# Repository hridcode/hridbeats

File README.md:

# hridBeats
hridBeats is an open-source sample chopper, synth, and MIDI controller based off the Raspberry Pi Pico. 

# Features

- 12 touchpads
- 8 potentiometers
- rotary encoder with a pushbutton
- joystick for mouse control
- TFT LCD 2.0" ST7789 display
- PCM5102A I2S DAC board for audio output
- SD card slot for loading songs/samples
- MIDI through USB
- Mini synth engine

# Pictures

|Schematic|PCB|Case|
|---|---|---|
||||

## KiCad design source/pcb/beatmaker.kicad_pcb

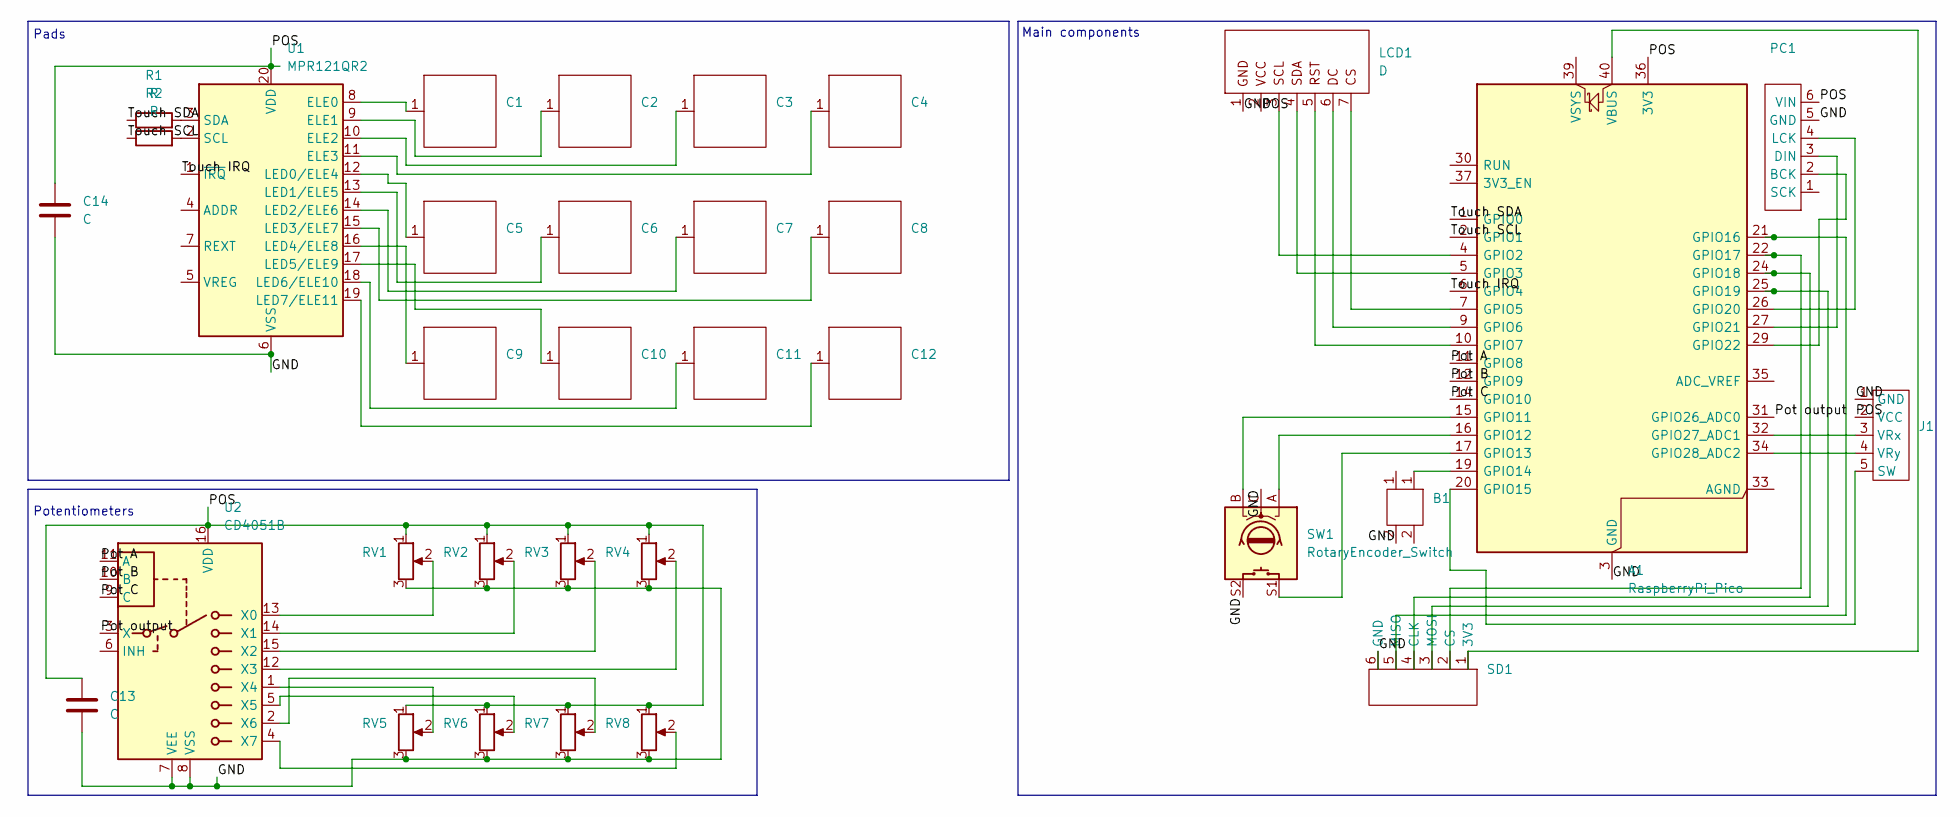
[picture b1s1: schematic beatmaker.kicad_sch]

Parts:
A1: RaspberryPi_Pico; RaspberryPi_Pico_Common_Unspecified
B1: SW_PUSH_6mm
C1, C2, C3, C4, C5, C6, C7, C8, C9, C10, C11, C12: copper_pad_25mm
C13, C14: C; CP_Radial_D4.0mm_P1.50mm
J1: ky-023-joystick
LCD1: D; ST7789
PC1: PCM5201-Board
R1, R2: R; R_Axial_DIN0204_L3.6mm_D1.6mm_P1.90mm_Vertical
RV1, RV2, RV3, RV4, RV5, RV6, RV7, RV8: R_Potentiometer; potentiometer
SD1: sd_card_module
SW1: RotaryEncoder_Switch; RotaryEncoder_Alps_EC11E-Switch_Vertical_H20mm_MountingHoles
U1: MPR121QR2; UQFN-20_3x3mm_P0.4mm
U2: CD4051B; DIP-16_W7.62mm

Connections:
/GND: A1.3 (GND), A1.8 (GND), A1.13 (GND), A1.18 (GND), A1.23 (GND), A1.28 (GND), A1.38 (GND), B1.2, C13.2, C14.2, J1.1 (GND), LCD1.1, PC1.5 (GND), RV1.3, RV2.3, RV3.3, RV4.3, RV5.3, RV6.3, RV7.3, RV8.3, SD1.6 (GND), SW1.C, SW1.S2, U1.6 (VSS), U2.7 (VEE), U2.8 (VSS)
/POS: A1.36 (3V3), C13.1, C14.1, J1.2 (VCC), LCD1.2, PC1.6 (VIN), RV1.1, RV2.1, RV3.1, RV4.1, RV5.1, RV6.1, RV7.1, RV8.1, U1.20 (VDD), U2.16 (VDD)
/Pot A: A1.11 (GPIO8), U2.11 (A)
/Pot B: A1.12 (GPIO9), U2.10 (B)
/Pot C: A1.14 (GPIO10), U2.9 (C)
/Pot output: A1.31 (GPIO26_ADC0), U2.3 (X)
/Touch IRQ: A1.6 (GPIO4), U1.1 (~IRQ)
/Touch SCL: A1.2 (GPIO1), R2.1
/Touch SDA: A1.1 (GPIO0), R1.1
unnamed: A1.4 (GPIO2), LCD1.3
unnamed: A1.5 (GPIO3), LCD1.4
unnamed: A1.7 (GPIO5), LCD1.7
unnamed: A1.9 (GPIO6), LCD1.6
unnamed: A1.10 (GPIO7), LCD1.5
unnamed: A1.15 (GPIO11), SW1.B
unnamed: A1.16 (GPIO12), SW1.A
unnamed: A1.17 (GPIO13), SW1.S1
unnamed: A1.19 (GPIO14), B1.1
unnamed: A1.20 (GPIO15), J1.5 (SW)
unnamed: A1.21 (GPIO16), SD1.5 (MISO)
unnamed: A1.22 (GPIO17), SD1.2 (CS)
unnamed: A1.24 (GPIO18), SD1.4 (CLK)
unnamed: A1.25 (GPIO19), SD1.3 (MOSI)
unnamed: A1.26 (GPIO20), PC1.4 (LCK)
unnamed: A1.27 (GPIO21), PC1.3 (DIN)
unnamed: A1.29 (GPIO22), PC1.2 (BCK)
unnamed: A1.32 (GPIO27_ADC1), J1.3 (VRx)
unnamed: A1.34 (GPIO28_ADC2), J1.4 (VRy)
unnamed: A1.40 (VBUS), SD1.1 (3V3)
unnamed: C1.1, U1.8 (ELE0)
unnamed: C2.1, U1.9 (ELE1)
unnamed: C3.1, U1.10 (ELE2)
unnamed: C4.1, U1.11 (ELE3)
unnamed: C5.1, U1.12 (LED0/ELE4)
unnamed: C6.1, U1.13 (LED1/ELE5)
unnamed: C7.1, U1.14 (LED2/ELE6)
unnamed: C8.1, U1.15 (LED3/ELE7)
unnamed: C9.1, U1.16 (LED4/ELE8)
unnamed: C10.1, U1.17 (LED5/ELE9)
unnamed: C11.1, U1.18 (LED6/ELE10)
unnamed: C12.1, U1.19 (LED7/ELE11)
unnamed: R2.2, U1.2 (SCL)
unnamed: R1.2, U1.3 (SDA)
unnamed: RV1.2, U2.13 (X0)
unnamed: RV2.2, U2.14 (X1)
unnamed: RV3.2, U2.15 (X2)
unnamed: RV4.2, U2.12 (X3)
unnamed: RV5.2, U2.1 (X4)
unnamed: RV6.2, U2.5 (X5)
unnamed: RV7.2, U2.2 (X6)
unnamed: RV8.2, U2.4 (X7)

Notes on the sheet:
Pads
Potentiometers
Main components

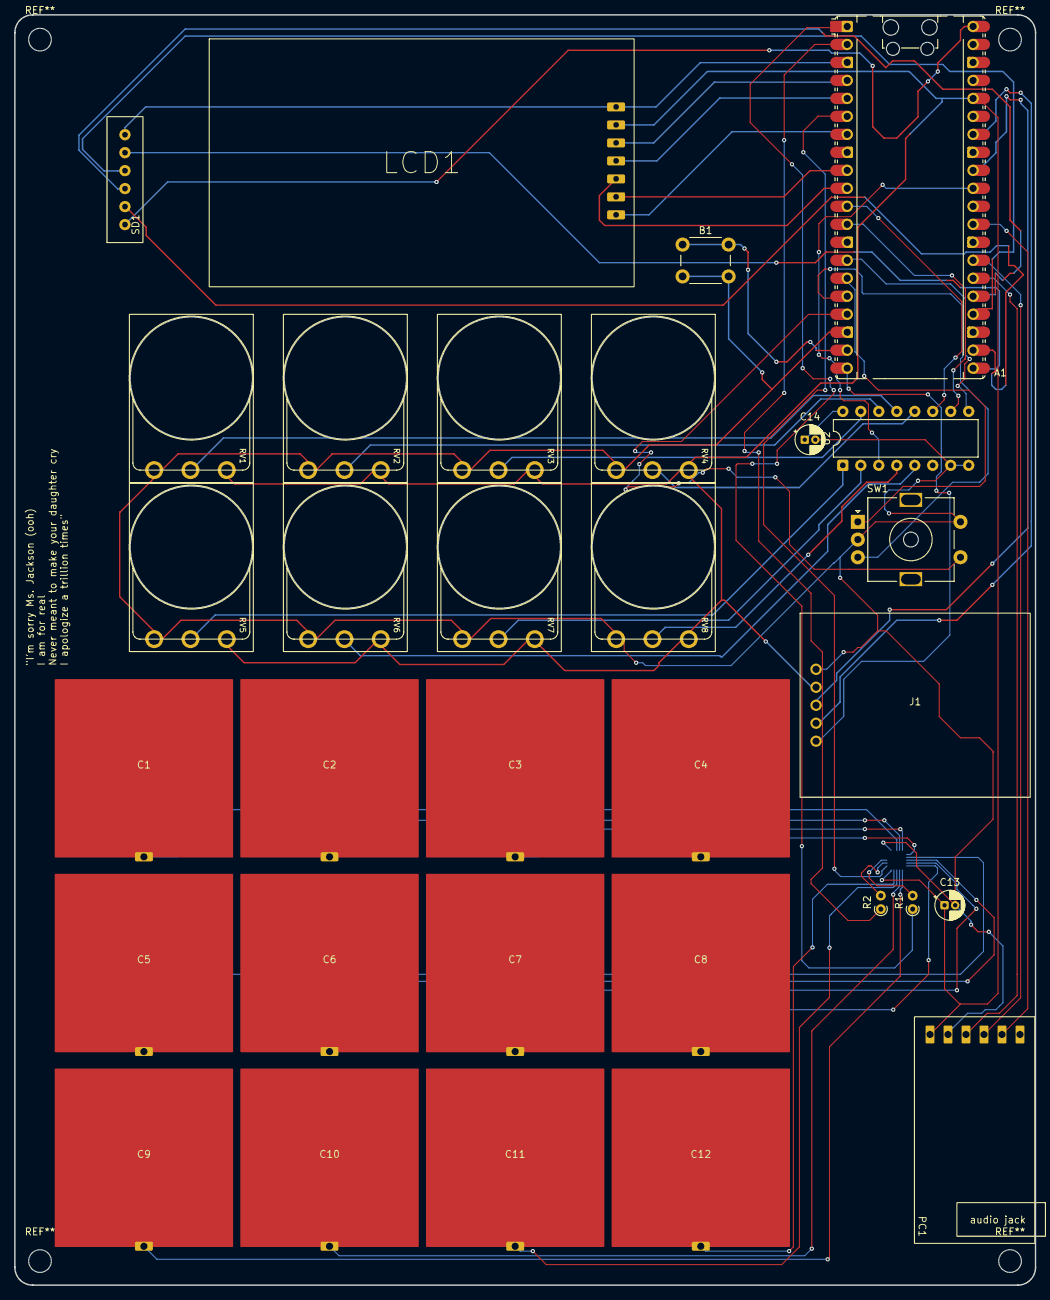
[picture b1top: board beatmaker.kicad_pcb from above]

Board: 2 copper layers, 144.2 x 179.4 mm, 33 parts (1 on the bottom side), 51 nets.

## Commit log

2026-03-20 Added source + production files
2026-03-20 Added photos
2026-03-20 Added BOM.csv
